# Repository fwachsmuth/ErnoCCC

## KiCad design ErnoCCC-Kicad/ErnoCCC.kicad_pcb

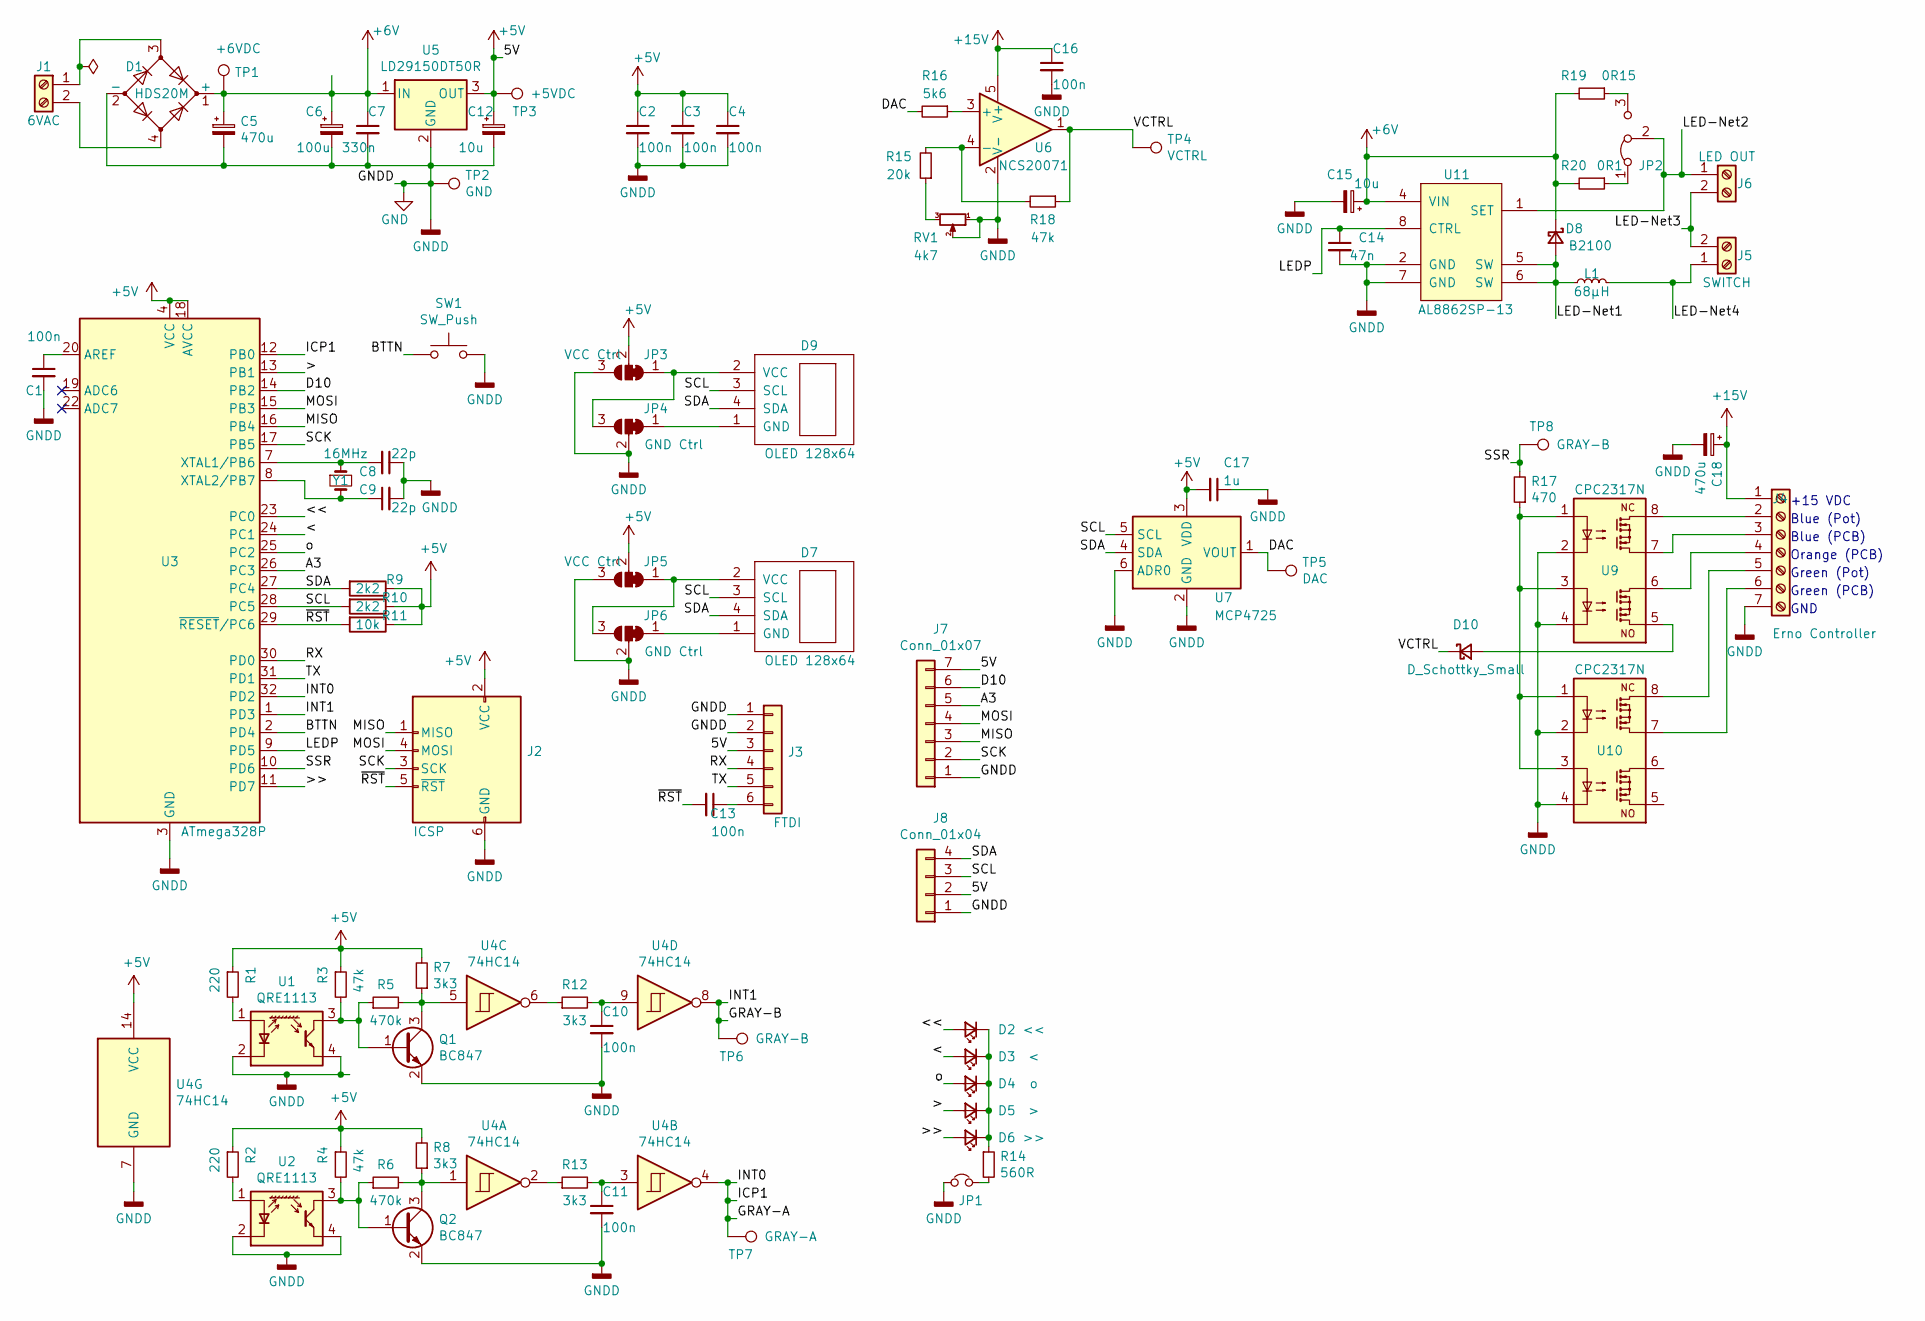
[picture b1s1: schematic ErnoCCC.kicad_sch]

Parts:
C1, C2, C3, C4, C10, C11, C13, C16: 100n; C_0805_2012Metric
C5, C18: 470u; CP_Elec_10x10
C6: 100u; CP_Elec_8x10.5
C7: 330n; C_0805_2012Metric
C8, C9: 22p; C_0805_2012Metric
C12, C15: 10u; CP_Elec_4x4.5
C14: 47n; C_0805_2012Metric
C17: 1u; C_0805_2012Metric
D1: HDS20M; HDS-4
D2: <<; LED_0805_2012Metric_Castellated
D3: <; LED_0805_2012Metric_Castellated
D4: o; LED_0805_2012Metric_Castellated
D5: >; LED_0805_2012Metric_Castellated
D6: >>; LED_0805_2012Metric_Castellated
D7: OLED 128x64; PinHeader_1x04_P2.54mm_Vertical
D8: B2100; D_SMB
D9: OLED 128x64; PinHeader_1x04_P2.54mm_Horizontal_shorter
D10: D_Schottky_Small; D_SMB
J1: 6VAC; TerminalBlock_bornier-2_P5.08mm
J2: ICSP; PinHeader_2x03_P2.54mm_Vertical
J3: FTDI; PinHeader_1x06_P2.54mm_Horizontal_shorter
J4: Erno Controller; TerminalBlock_Phoenix_MPT-0,5-7-2.54_1x07_P2.54mm_Horizontal
J5: SWITCH; TerminalBlock_bornier-2_P5.08mm
J6: LED OUT; TerminalBlock_bornier-2_P5.08mm
J7: Conn_01x07; PinSocket_1x07_P2.54mm_Vertical
J8: Conn_01x04; PinHeader_1x04_P2.54mm_Vertical
JP1: LED Jumper; PinHeader_1x03_P2.54mm_Vertical
JP2: R1 Select; SolderJumper-3_P1.3mm_Bridged2Bar12_Pad1.0x1.5mm
JP3, JP5: VCC Ctrl; SolderJumper-3_P1.3mm_Bridged12_RoundedPad1.0x1.5mm
JP4, JP6: GND Ctrl; SolderJumper-3_P1.3mm_Bridged12_RoundedPad1.0x1.5mm
L1: 68µH; L_10.4x10.4_H4.8
Q1, Q2: BC847; SOT-23
R1, R2: 220; R_0805_2012Metric
R3, R4, R18: 47k; R_0805_2012Metric
R5, R6: 470k; R_0805_2012Metric
R7, R8, R12, R13: 3k3; R_0805_2012Metric
R9, R10: 2k2; R_0805_2012Metric
R11: 10k; R_0805_2012Metric
R14: 560R; R_0805_2012Metric
R15: 20k; R_0805_2012Metric
R16: 5k6; R_0805_2012Metric
R17: 470; R_0805_2012Metric
R19: 0R15; R_1210_3225Metric
R20: 0R1; R_1210_3225Metric
RV1: 4k7; Potentiometer_Bourns_3296W_Vertical
SW1: SW_Push; SW_PUSH_6mm_H7.3mm
TP1: +6VDC; TestPoint_THTPad_D1.5mm_Drill0.7mm
TP2: GND; TestPoint_THTPad_2.0x2.0mm_Drill1.0mm
TP3: +5VDC; TestPoint_THTPad_D1.5mm_Drill0.7mm
TP4: VCTRL; TestPoint_THTPad_1.5x1.5mm_Drill0.7mm
TP5: DAC; TestPoint_THTPad_1.5x1.5mm_Drill0.7mm
TP6, TP8: GRAY-B; TestPoint_THTPad_1.5x1.5mm_Drill0.7mm
TP7: GRAY-A; TestPoint_THTPad_1.5x1.5mm_Drill0.7mm
U1, U2: QRE1113; QRE1113GR-slim
U3: ATmega328P; TQFP-32_7x7mm_P0.8mm
U4: 74HC14; SOIC-14_3.9x8.7mm_P1.27mm
U5: LD29150DT50R; TO-252-2
U6: NCS20071; TSOT-23-5
U7: MCP4725; SOT-23-6
U9, U10: CPC2317N; SOIC-8
U11: AL8862SP-13; SOIC-8-1EP_3.9x4.9mm_P1.27mm_EP2.41x3.81mm_ThermalVias
Y1: 16MHz; Crystal_SMD_Abracon_ABM3-2Pin_5.0x3.2mm

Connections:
+5V: C2.1, C3.1, C4.1, C12.1, C17.2, J2.2 (VCC), J3.3, J7.7, J8.2, JP3.2 (C), JP5.2 (C), R1.1, R2.1, R3.1, R4.1, R7.2, R8.2, R9.1, R10.1, R11.1, TP3.1, U3.4 (VCC), U3.6 (VCC), U3.18 (AVCC), U4.14 (VCC), U5.3 (OUT), U7.3 (VDD)
+6V: C5.1, C6.1, C7.1, C15.1, D1.1 (+), D8.1 (K), R19.2, R20.2, TP1.1, U5.1 (IN), U11.4 (VIN)
+15V: C16.1, C18.1, J4.1, U6.5 (V+)
/<: D3.2 (A), U3.24 (PC1)
/<<: D2.2 (A), U3.23 (PC0)
/>: D5.2 (A), U3.13 (PB1)
/>>: D6.2 (A), U3.11 (PD7)
/A3: J7.5, U3.26 (PC3)
/BTTN: SW1.1, U3.2 (PD4)
/D10: J7.6, U3.14 (PB2)
/DAC: R16.2, TP5.1, U7.1 (VOUT)
/GRAY-A: TP7.1, U3.12 (PB0), U3.32 (PD2), U4.4
/GRAY-B: TP6.1, U3.1 (PD3), U4.8
/LED-Net1: D8.2 (A), L1.1, U11.5 (SW), U11.6 (SW)
/LED-Net2: J6.1, JP2.2 (C), U11.1 (SET)
/LED-Net3: J5.2, J6.2
/LED-Net4: J5.1, L1.2
/LEDP: C14.1, U3.9 (PD5), U11.8 (CTRL)
/MISO: J2.1 (MISO), J7.3, U3.16 (PB4)
/MOSI: J2.4 (MOSI), J7.4, U3.15 (PB3)
/RX: J3.4, U3.30 (PD0)
/SCK: J2.3 (SCK), J7.2, U3.17 (PB5)
/SCL: D7.3 (SCL), D9.3 (SCL), J8.3, R10.2, U3.28 (PC5), U7.5 (SCL)
/SDA: D7.4 (SDA), D9.4 (SDA), J8.4, R9.2, U3.27 (PC4), U7.4 (SDA)
/SSR: R17.2, TP8.1, U3.10 (PD6)
/TX: J3.5, U3.31 (PD1)
/VCTRL: D10.1 (K), R18.1, TP4.1, U6.1
/o: D4.2 (A), U3.25 (PC2)
/~RST: C13.2, J2.5 (~RST), R11.2, U3.29 (~RESET/PC6)
GND: C1.2, C2.2, C3.2, C4.2, C5.2, C6.2, C7.2, C8.1, C9.2, C10.2, C11.2, C12.2, C14.2, C15.2, C16.2, C17.1, C18.2, D1.2 (-), J2.6 (GND), J3.1, J3.2, J4.7, J7.1, J8.1, JP1.1, JP3.3 (B), JP4.2 (C), JP5.3 (B), JP6.2 (C), Q1.2 (E), Q2.2 (E), RV1.1, RV1.2, SW1.2, TP2.1, U1.2 (K), U1.4, U2.2 (K), U2.4, U3.3 (GND), U3.5 (GND), U3.21 (GND), U4.7 (GND), U5.2 (GND), U6.2 (V-), U7.2 (GND), U7.6 (ADR0), U9.2, U9.4, U10.2, U10.4, U11.2 (GND), U11.7 (GND)
unnamed: C1.1, U3.20 (AREF)
unnamed: C8.2, U3.7 (XTAL1/PB6), Y1.1
unnamed: C9.1, U3.8 (XTAL2/PB7), Y1.2
unnamed: C10.1, R12.2, U4.9
unnamed: C11.1, R13.2, U4.3
unnamed: C13.1, J3.6
unnamed: D1.3, J1.1
unnamed: D1.4, J1.2
unnamed: D2.1 (K), D3.1 (K), D4.1 (K), D5.1 (K), D6.1 (K), R14.1
unnamed: D7.1 (GND), JP6.1 (A)
unnamed: D7.2 (VCC), JP5.1 (A), JP6.3 (B)
unnamed: D9.1 (GND), JP4.1 (A)
unnamed: D9.2 (VCC), JP3.1 (A), JP4.3 (B)
unnamed: D10.2 (A), U9.5
unnamed: J4.2, U9.8
unnamed: J4.3, U9.7
unnamed: J4.4, U9.6
unnamed: J4.5, U10.8
unnamed: J4.6, U10.7
unnamed: JP1.2, R14.2
unnamed: JP2.1 (A), R20.1
unnamed: JP2.3 (B), R19.1
unnamed: Q1.1 (B), R3.2, R5.1, U1.3
unnamed: Q1.3 (C), R5.2, R7.1, U4.5
unnamed: Q2.1 (B), R4.2, R6.1, U2.3
unnamed: Q2.3 (C), R6.2, R8.1, U4.1
unnamed: R1.2, U1.1 (A)
unnamed: R2.2, U2.1 (A)
unnamed: R12.1, U4.6
unnamed: R13.1, U4.2
unnamed: R15.1, RV1.3
unnamed: R15.2, R18.2, U6.4 (-)
unnamed: R16.1, U6.3 (+)
unnamed: R17.1, U9.1, U9.3, U10.1, U10.3

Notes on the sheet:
GND
+15 VDC
Green (PCB)
Blue (Pot)
Green (Pot)
Orange (PCB)
Blue (PCB)

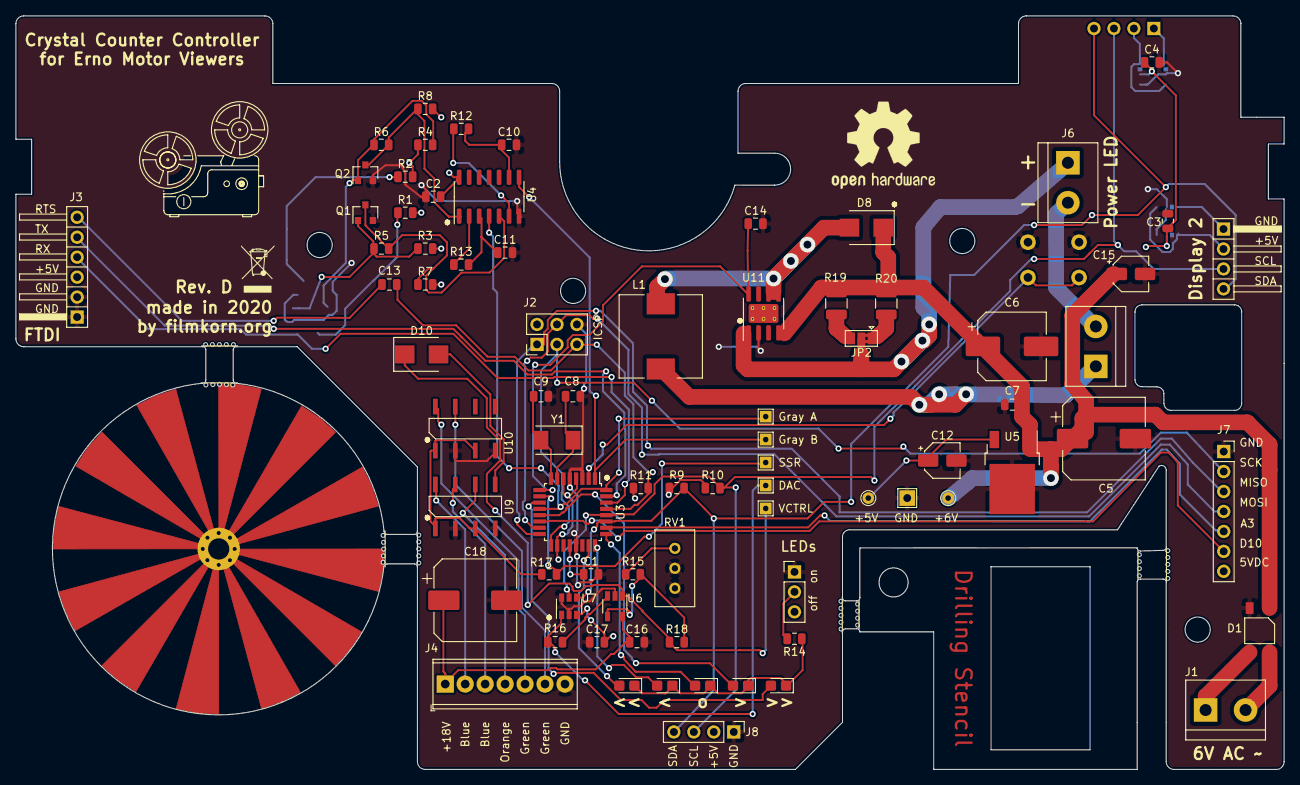
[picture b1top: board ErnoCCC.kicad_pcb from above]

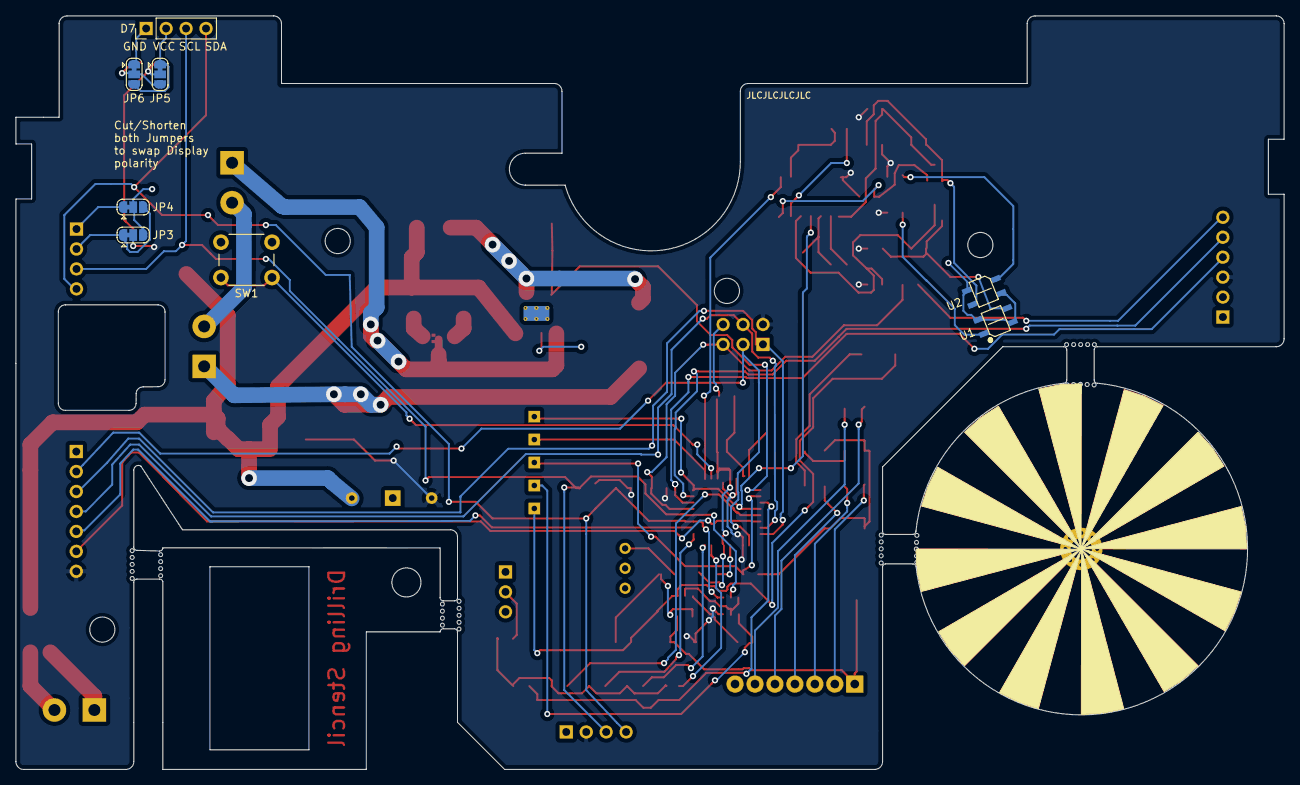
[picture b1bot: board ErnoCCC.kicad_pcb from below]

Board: 2 copper layers, 161.4 x 95.9 mm, 86 parts (8 on the bottom side), 64 nets.

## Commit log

2019-12-28 Initial Code Snippets
2019-12-28 KiCad Project
2019-12-28 Cleaning up Dir Structure
2019-12-28 Adding Code Snippets that might be useful on the retreat weekend
2019-12-29 Gerbers for Rev A
2019-12-29 Cleaning up Kicad
2019-12-30 Adding a D10 Breakout for later Vectrol (or MOSFET) experiments
2019-12-30 Adding TPs to a Header, fixing disconnected GND planes
2019-12-30 Create a little jittering GRAY-Code Generator to simulate viewer movenment
2019-12-31 SMPTE Display works, but is a tad too slow @ 7.7 fps
2019-12-31 Fixing I2C Pullups Rs, removing invalid Gerbers
2019-12-31 Draw only those digits that changed
2019-12-31 All the Kalle contributions :O
2019-12-31 Enable Subframe Display
2020-01-01 So. Much. Kalle. Magic.
2020-01-01 Just stremalining some var names
2020-01-01 Some more cleanup
2020-01-01 Just some refactoring & cleanup
2020-01-01 Updating to bigger (and curved) MouseBites to match JLCPCB's DRCs
2020-01-01 Added “Stopped” and “Running” states Changed a lot of other stuff
    -Kalle
2020-01-01 Kalles Stand (unfertig)
2020-01-02 Implemented correct way of handling 16 2/3 fps subframes
    -Kalle
2020-01-02 Reset by long press in stopped mode Less rewriting the time Fixed bugs
    -Kalle
2020-01-02 Fixing i2c bus, making OLED polarity conifgurable, submitting final ReV gerbers
2020-01-02 Saving some RAM
2020-01-02 Adding Todos and Roadmap
2020-01-02 Just annotating my question marks
2020-01-02 Few more comments
2020-01-02 Idling in the reset counter menu will hide it again A counter change will also hide it 9 fps has only one digit Added compiler macros Decreased the time redraws
    -Kalle
2020-01-02 minor bug fix
2020-01-02 Adding persisting to EEPROM (by Kalle)
2020-01-02 Adding original Erno Controller Schematics
2020-01-05 Schema Refactoring in progress...
2020-01-11 preparing for rev b
2020-01-12 Preparing for the big refactoring (old footprints still there)
2020-01-12 Preparing for the big RevB rerouting
2020-01-13 Updating Todos
2020-01-14 Adding a 15VDC Elko
2020-01-15 Reduced Footprint size of C12 and C15 Eliminated upper right slot for flatter PCB mounting Made the bottom right cutout 2.5mm bigger to have less stress on the viewer's mirror when mounting the PCB
2020-01-15 Updating the Pin Header Length (6x done, 4x and 7x to follow)
2020-01-15 Todos
2020-01-16 Updating QRE1113 footrpint
2020-01-16 Smaller Header footprint for 4 & 5 pin connectors
2020-01-16 Correcting Display Position
2020-01-16 Fixing Schematics Bugs, PCB progress
2020-01-16 Spreading out parts
2020-01-16 Re-Routed 99%
2020-01-17 Wiring it all up
2020-01-17 More wires
2020-01-17 DRC green!
2020-01-17 Fixing Encoder Direction, improving Silkscreen
2020-01-17 Ready for Rev.C
2020-01-18 Adding fidicules for the stencil
2020-01-18 dding a negative outline PCB for easier solder paste application
2020-01-18 Rounding Corners, making fidicules actually match
2020-01-18 Rounding some corners
2020-01-18 Rev.B as ordered
2020-01-18 Board validations while waiting fro RevB to ship
2020-01-19 Fixing the Frequency Display
2020-01-19 Trying to fix the missing solder mask on the stencil board probably still needs a net though
2020-01-19 Trying to fix the button
2020-01-19 Introducing Software Stop Detection
2020-01-19 Eliminating the stopPin
2020-01-20 Fixing the 16.66 Eprom bug
2020-01-24 New BOM
2020-02-01 Freezing last state before getting into motor control
2020-02-01 First kinda working commit
2020-02-01 start with a new sync point, no need to catch up differences from before
2020-02-01 Auto Calibrate 0.1! :)
2020-02-02 Dynamic Measurement Cycle Length
2020-02-02 Smarter dynamics measuerments, todos
2020-02-02 Extrapolate Ctrl Voltages after determining just two voltages
2020-02-02 Added EEPROM Calibration saving
2020-02-02 Trying to debug why regulation doesn't work
2020-02-02 Less debug output
2020-02-02 Fixed the reflection glitch on GRAY-A, found out that the projector counter counts only half as fast as the timer. Temp fixed by double increments
2020-02-02 Cleanup
2020-02-02 Using every Change now in ISR, doubling responsiveness \o/
2020-02-03 Getting excited about potential EDL support
2020-02-16 Trying to make the controller fps agnostic
2020-02-16 It's kind a working now. Why? Not sure.
2020-02-16 Show "18.00 fps" when locked (extra digits)
2020-02-16 It oddly works, but how is fpsState = 6 being treated as being 1?
2020-02-16 Added wider regulation range, and now something become magic smoke
2020-02-17 Dis lookin good. Opamp swapped.
2020-02-23 Preparing RevC. One Diode still missing
2020-02-23 Fixed Exe Distance, fixed Display Position, fixed missing i2c on DAC, added Diode to Motor Out, Added labels to pinouts, removed Peephole LED
2020-02-23 Adding comments re how to calibrate the trimpot (new R15 value needed!)
2020-02-23 Gute Nacht
2020-02-24 Updating Connectors for RevC
2020-02-24 Adding all the Improvements: SPI, TPs for DAV, VCTRL, SSR, GRAY. Also, GND and VCC on J7
2020-02-25 Adding I2C on a pinheader
2020-02-25 RevC: Done!
2020-02-25 Gerbers for Rev C
2020-03-07 Pins have changed in RevC. Fixing this here
2020-03-07 Fixing the short in the LEDs :(
2020-03-07 Fixing all the GND plane errors
2020-03-07 More cleanup, better ground planes
2020-03-07 Adding Trimpot calibration mode
2020-03-07 Fixing some silkscreen
2020-03-07 Adding Status Display for Calibration Mode
2020-03-08 Speed Calibration now happening by pushing the button and turning on the motor
2020-03-08 Calibration becoming nice.
2020-03-08 Updating the Display after calibration
2020-03-08 Adding some LED feedback to the calibration process
2020-03-08 Fixing Reset! (Kalle ftw)
2020-03-08 Nulldurchgnag gefixt (Kalle)
2023-11-20 Kicad 6 files, .gitignore
2023-11-20 Removing KiCad backup stuff
